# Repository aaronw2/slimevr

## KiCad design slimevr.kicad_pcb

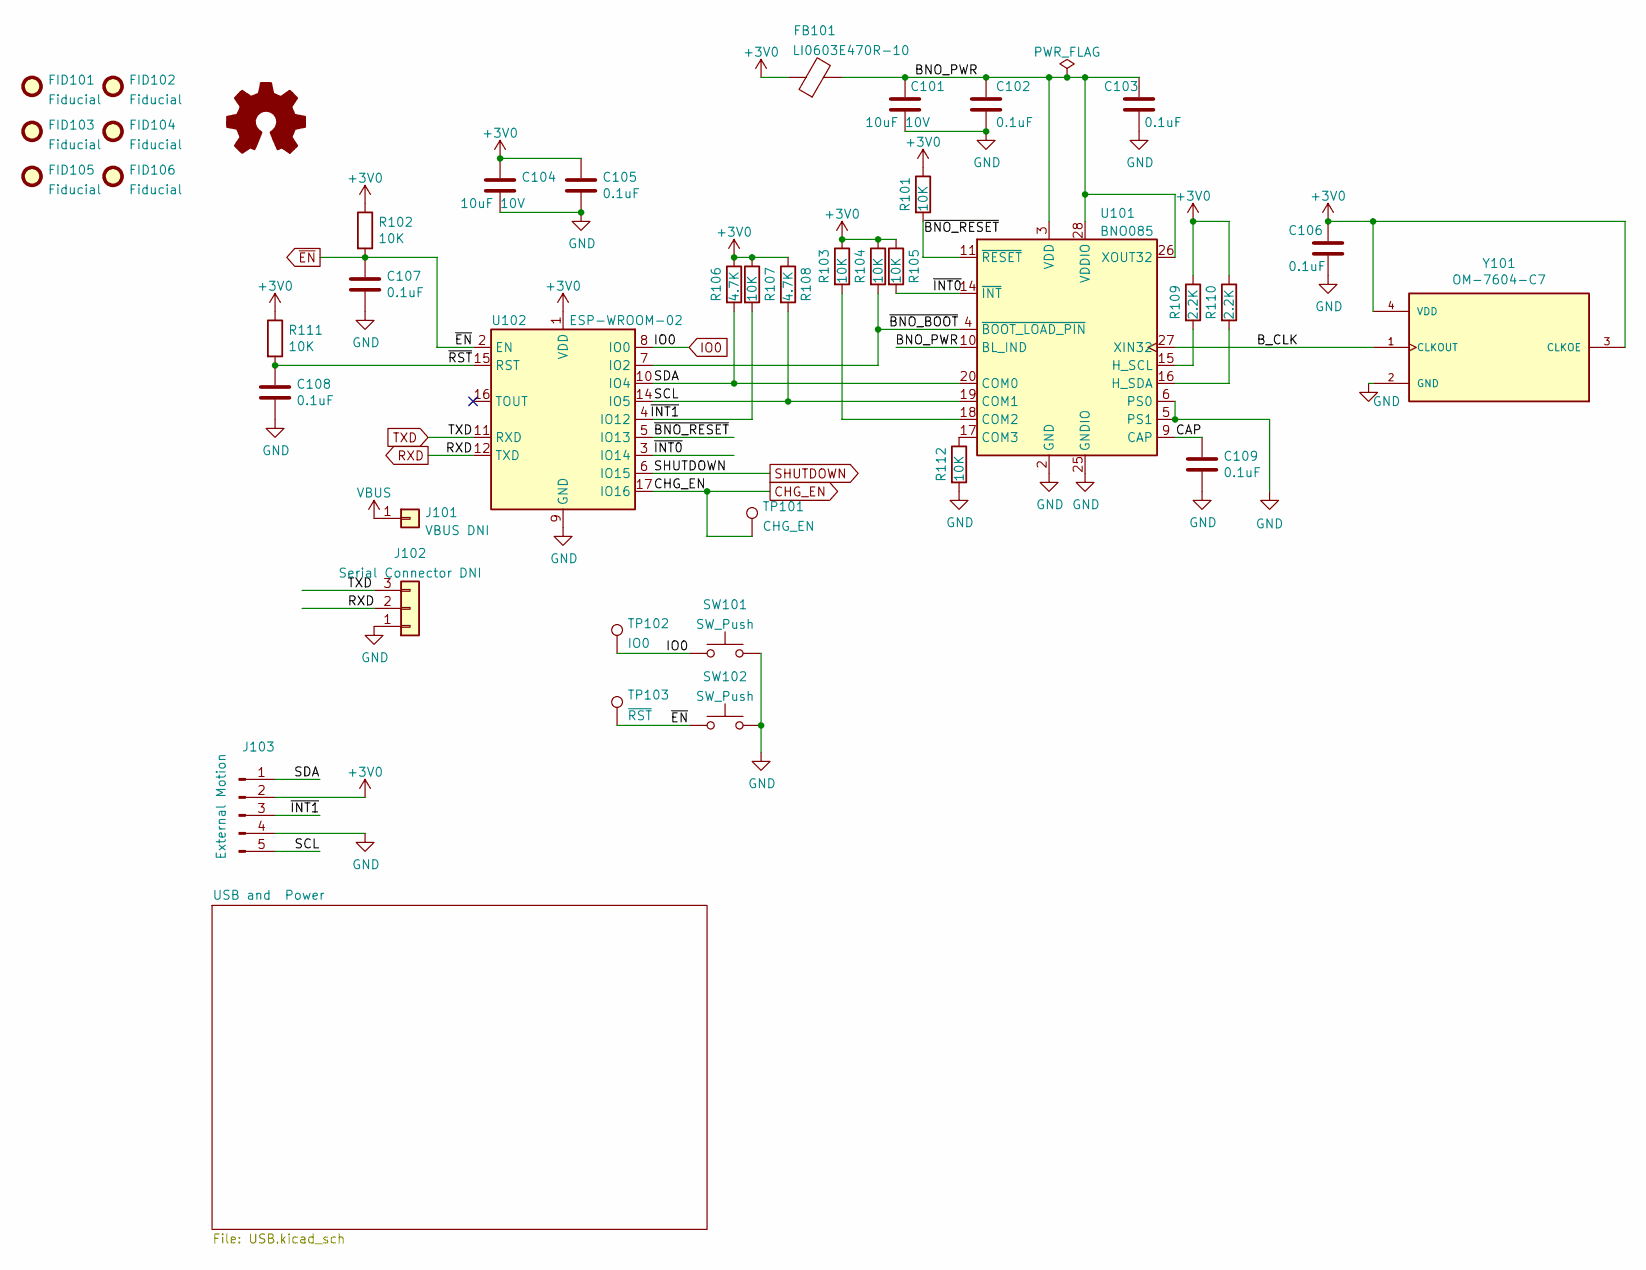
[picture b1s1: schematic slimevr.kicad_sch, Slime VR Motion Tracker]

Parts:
C101, C104: 10uF 10V; C_0603_1608Metric; MPN CL10A106MP8NNNC
C102, C103, C105, C106, C107, C108, C109: 0.1uF; C_0603_1608Metric; MPN C0603C104M3RAC7867
FB101: LI0603E470R-10; L_0603_1608Metric; MPN LI0603E470R-10
FID101, FID102, FID103, FID104, FID105, FID106: Fiducial; Fiducial_0.5mm_Mask1mm
J101: VBUS DNI; PinHeader_1x01_P2.54mm_Vertical
J102: Serial Connector DNI; PinHeader_1x03_P2.54mm_Vertical
J103: External Motion; JST_PH_S5B-PH-K_1x05_P2.00mm_Horizontal; MPN B5B-PH-SM4-TBT(LF)(SN)
LOGO101: Logo_Open_Hardware_Small; OSHW-Logo2_7.3x6mm_SilkScreen
R101, R102, R103, R104, R105, R107, R111, R112: 10K; R_0603_1608Metric; MPN RC0603FR-0710KL
R106, R108: 4.7K; R_0603_1608Metric; MPN RC0603FR-074K7L
R109, R110: 2.2K; R_0603_1608Metric; MPN RC0603FR-074K7L
SW101, SW102: SW_Push; SW_SPST_CK_KXT3; MPN KXT 331 LHS
TP101: CHG_EN; TestPoint_THTPad_1.0x1.0mm_Drill0.5mm
TP102: IO0; TestPoint_THTPad_1.0x1.0mm_Drill0.5mm
TP103: ~{RST}; TestPoint_THTPad_1.0x1.0mm_Drill0.5mm
U101: BNO085; LGA-28_5.2x3.8mm_P0.5mm; MPN BNO085
U102: ESP-WROOM-02; MPN ESP-WROOM-02D (4MB)
Y101: OM-7604-C7; OSC_OM-7604-C7; PARTREV 4.2/06.2019

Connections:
+3V0: C104.1, C105.1, C106.1, FB101.1, J103.2, R101.1, R102.1, R103.1, R104.1, R105.1, R106.1, R107.1, R108.1, R109.1, R110.1, R111.1, U102.1 (VDD), Y101.3 (CLKOE), Y101.4 (VDD); also elsewhere on the board
/BNO_PWR: C101.1, C102.1, C103.1, FB101.2, U101.3 (VDD), U101.10 (BL_IND), U101.26 (XOUT32), U101.28 (VDDIO)
/B_CLK: U101.27 (XIN32), Y101.1 (CLKOUT)
/CAP: C109.1, U101.9 (CAP)
/SCL: J103.5, R108.2, U101.19 (COM1), U102.14 (IO5)
/SDA: J103.1, R106.2, U101.20 (COM0), U102.10 (IO4)
/~BNO_BOOT: R104.2, U101.4 (~BOOT_LOAD_PIN), U102.7 (IO2)
/~BNO_RESET: R101.2, U101.11 (~RESET), U102.5 (IO13)
/~INT0: R105.2, U101.14 (~INT), U102.3 (IO14)
/~INT1: J103.3, R107.2, U102.4 (IO12)
/~RST: C108.1, R111.2, U102.15 (RST)
CHG_EN: TP101.1, U102.17 (IO16); also elsewhere on the board
GND: C101.2, C102.2, C103.2, C104.2, C105.2, C106.2, C107.2, C108.2, C109.2, J102.1, J103.4, R112.2, SW101.2, SW102.2, U101.2 (GND), U101.5 (PS1), U101.6 (PS0), U101.25 (GNDIO), U102.9 (GND), U102.13 (GND), U102.18 (GND), U102.19 (GND), Y101.2 (GND); also elsewhere on the board
IO0: SW101.1, TP102.1, U102.8 (IO0); also elsewhere on the board
unnamed: R103.2, U101.18 (COM2)
unnamed: R112.1, U101.17 (COM3)
unnamed: R109.2, U101.15 (H_SCL)
unnamed: R110.2, U101.16 (H_SDA)
RXD: J102.2, U102.12 (TXD); also elsewhere on the board
SHUTDOWN: U102.6 (IO15); also elsewhere on the board
TXD: J102.3, U102.11 (RXD); also elsewhere on the board
VBUS: J101.1; also elsewhere on the board
~EN: C107.1, R102.2, SW102.1, TP103.1, U102.2 (EN); also elsewhere on the board

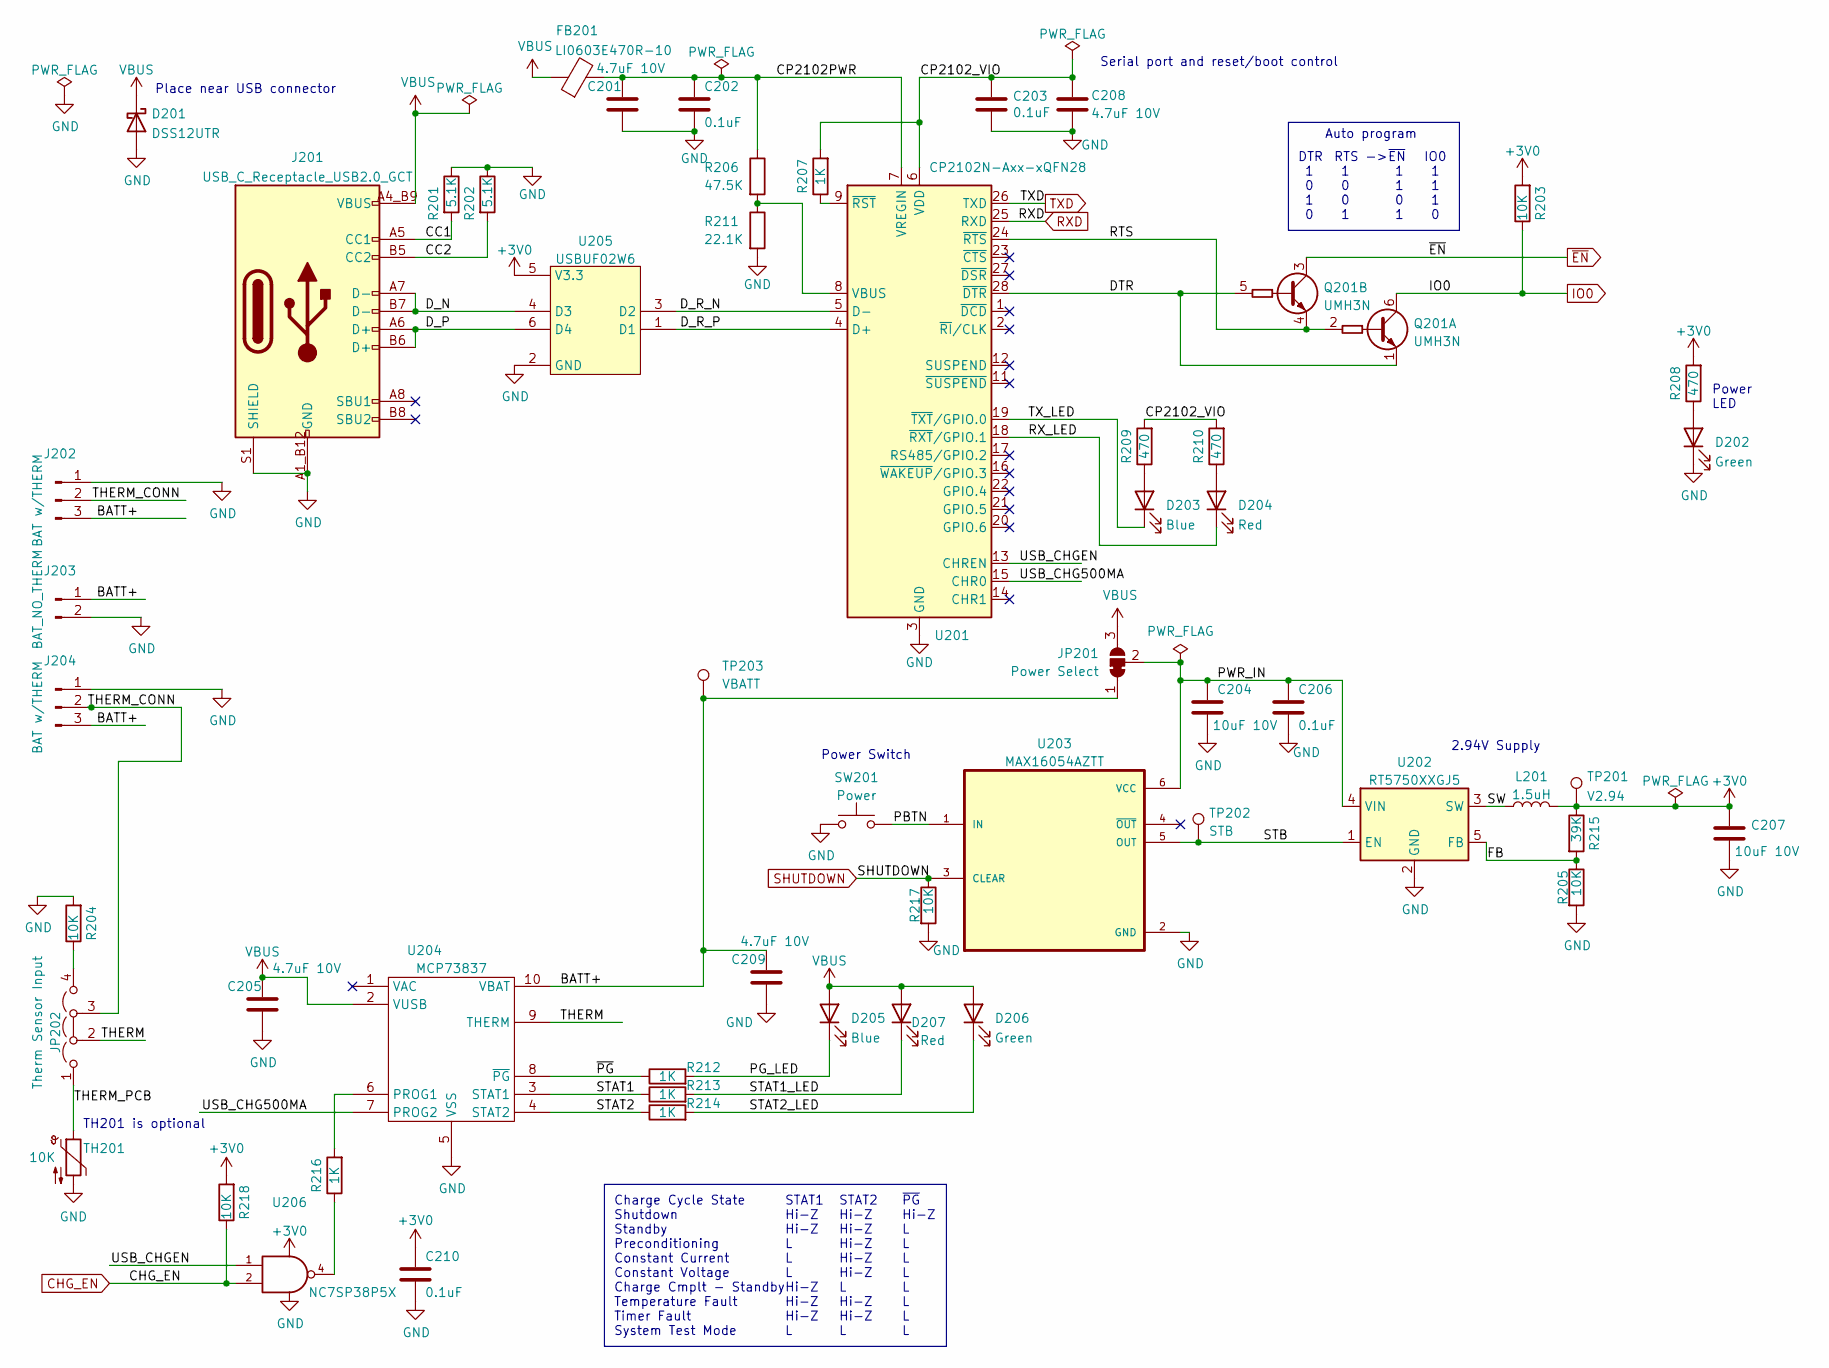
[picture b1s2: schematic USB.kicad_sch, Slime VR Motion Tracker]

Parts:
C201, C205, C208, C209: 4.7uF 10V; C_0603_1608Metric; MPN CL10A475KP8NNNC
C202, C203, C206, C210: 0.1uF; C_0603_1608Metric; MPN C0603C104M3RAC7867
C204, C207: 10uF 10V; C_0603_1608Metric; MPN CL10A106MP8NNNC
D201: DSS12UTR; D_SOD-123F; MPN DSS12UTR
D202, D206: Green; LED_0603_1608Metric; MPN 150060VS55040
D203, D205: Blue; LED_0603_1608Metric; MPN 150060BS55040
D204, D207: Red; LED_0603_1608Metric; MPN 150060SS55040
FB201: LI0603E470R-10; L_0603_1608Metric; MPN LI0603E470R-10
J201: USB_C_Receptacle_USB2.0_GCT; GCT_USB4105-GF-A; MPN USB4105-GF-A
J202: BAT w/THERM; SolderWire-0.1sqmm_1x03_P3.6mm_D0.4mm_OD1mm
J203: BAT_NO_THERM; JST_PH_S2B-PH-K_1x02_P2.00mm_Horizontal; MPN B2B-PH-SM4-TB(LF)(SN)
J204: BAT w/THERM; Molex_PicoBlade_53048-0310_1x03_P1.25mm_Horizontal; MPN 0530480350
JP201: Power Select; SolderJumper-3_P1.3mm_Bridged12_RoundedPad1.0x1.5mm
JP202: Therm Sensor Input; SolderJumper-4_P1.3mm_Bridged23_RoundedPad1.0x1.5mm
L201: 1.5uH; L_1008_2520Metric; MPN DFE252010F-1R5M=P2
Q201: UMH3N; SOT-363_SC-70-6
R201, R202: 5.1K; R_0603_1608Metric; MPN RC0603FR-075K1L
R203, R204, R205, R217, R218: 10K; R_0603_1608Metric; MPN RC0402FR-070RL
R206: 47.5K; R_0603_1608Metric
R207, R212, R213, R214, R216: 1K; R_0603_1608Metric; MPN RC0603FR-071KL
R208, R209, R210: 470; R_0603_1608Metric; MPN RC0603FR-07470RL
R211: 22.1K; R_0603_1608Metric
R215: 39K; R_0603_1608Metric; MPN RC0603FR-0739KL
SW201: Power; Panasonic_EVQPUL_EVQPUC; MPN EVQ-PUD02K
TH201: 10K; R_0603_1608Metric; MPN NCU18XH103E60RB
TP201: V2.94; TestPoint_Keystone_5000-5004_Miniature
TP202: STB; TestPoint_THTPad_1.0x1.0mm_Drill0.5mm
TP203: VBATT; TestPoint_THTPad_1.0x1.0mm_Drill0.5mm
U201: CP2102N-Axx-xQFN28; QFN-28-1EP_5x5mm_P0.5mm_EP3.35x3.35mm; MPN CP2102N-A02-GQFN28R
U202: RT5750XXGJ5; TSOT-23-5; MPN RT5750BHGJ5
U203: MAX16054AZTT; TSOT-23-6; MPN MAX16054AZT+T
U204: MCP73837; DFN-10-1EP_3x3mm_P0.5mm_EP1.55x2.48mm; MPN MCP73837-FJI/MF
U205: USBUF02W6; SOT-323-6L
U206: NC7SP38P5X; SOT-353_SC-70-5

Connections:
+3V0: C207.1, C210.1, L201.2, R203.2, R208.2, R215.1, R218.2, TP201.1, U205.5 (V3.3), U206.5 (VCC); also elsewhere on the board
/USB and Power/BATT+: C209.1, J202.3, J203.1, J204.3, JP201.1 (A), TP203.1, U204.10 (VBAT)
/USB and Power/CC1: J201.A5 (CC1), R201.2
/USB and Power/CC2: J201.B5 (CC2), R202.2
/USB and Power/CP2102PWR: C201.1, C202.1, FB201.2, R206.1, U201.7 (VREGIN)
/USB and Power/CP2102_VIO: C203.1, C208.1, R207.2, R209.2, R210.2, U201.6 (VDD)
/USB and Power/DTR: Q201.1 (E1), Q201.5 (B2), U201.28 (~DTR)
/USB and Power/D_N: J201.A7 (D-), J201.B7 (D-), U205.4 (D3)
/USB and Power/D_P: J201.A6 (D+), J201.B6 (D+), U205.6 (D4)
/USB and Power/D_R_N: U201.5 (D-), U205.3 (D2)
/USB and Power/D_R_P: U201.4 (D+), U205.1 (D1)
/USB and Power/FB: R205.1, R215.2, U202.5 (FB)
/USB and Power/PBTN: SW201.2, U203.1 (IN)
/USB and Power/PG_LED: D205.1 (K), R212.2
/USB and Power/PWR_IN: C204.1, C206.1, JP201.2 (C), U202.4 (VIN), U203.6 (VCC)
/USB and Power/RTS: Q201.2 (B1), Q201.4 (E2), U201.24 (~RTS)
/USB and Power/RX_LED: D204.1 (K), U201.18 (~RXT/GPIO.1)
/USB and Power/STAT1: R213.1, U204.3 (STAT1)
/USB and Power/STAT1_LED: D207.1 (K), R213.2
/USB and Power/STAT2: R214.1, U204.4 (STAT2)
/USB and Power/STAT2_LED: D206.1 (K), R214.2
/USB and Power/STB: TP202.1, U202.1 (EN), U203.5 (OUT)
/USB and Power/SW: L201.1, U202.3 (SW)
/USB and Power/THERM: JP202.2 (C), U204.9 (THERM)
/USB and Power/THERM_CONN: J202.2, J204.2, JP202.3 (B)
/USB and Power/THERM_PCB: JP202.1 (A), TH201.1
/USB and Power/TX_LED: D203.1 (K), U201.19 (~TXT/GPIO.0)
/USB and Power/USB_CHG500MA: U201.15 (CHR0), U204.7 (PROG2)
/USB and Power/USB_CHGEN: U201.13 (CHREN), U206.1 (A)
/USB and Power/~PG: R212.1, U204.8 (~PG)
CHG_EN: R218.1, U206.2 (B); also elsewhere on the board
GND: C201.2, C202.2, C203.2, C204.2, C205.2, C206.2, C207.2, C208.2, C209.2, C210.2, D201.2 (A), D202.1 (K), J201.A1_B12 (GND), J201.B1_A12 (GND), J201.S1 (SHIELD), J201.S2 (SHIELD), J201.S3 (SHIELD), J201.S4 (SHIELD), J202.1, J203.2, J204.1, R201.1, R202.1, R204.2, R205.2, R211.2, R217.2, SW201.1, TH201.2, U201.3 (GND), U201.29 (GND), U202.2 (GND), U203.2 (GND), U204.5 (VSS), U204.11 (VSS), U205.2 (GND), U206.3 (GND); also elsewhere on the board
IO0: Q201.6 (C1), R203.1; also elsewhere on the board
unnamed: D202.2 (A), R208.1
unnamed: D203.2 (A), R209.1
unnamed: D204.2 (A), R210.1
unnamed: JP202.4, R204.1
unnamed: R206.2, R211.1, U201.8 (VBUS)
unnamed: R207.1, U201.9 (~RST)
unnamed: R216.1, U206.4 (Y)
unnamed: R216.2, U204.6 (PROG1)
RXD: U201.25 (RXD); also elsewhere on the board
SHUTDOWN: R217.1, U203.3 (CLEAR); also elsewhere on the board
TXD: U201.26 (TXD); also elsewhere on the board
VBUS: C205.1, D201.1 (K), D205.2 (A), D206.2 (A), D207.2 (A), FB201.1, J201.A4_B9 (VBUS), J201.B4_A9 (VBUS), JP201.3 (B), U204.2 (VUSB); also elsewhere on the board
~EN: Q201.3 (C2); also elsewhere on the board

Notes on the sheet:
Power Switch
Charge Cycle State Shutdown Standby Preconditioning Constant Current Constant Voltage Charge Cmplt - Standby Temperature Fault Timer Fault System Test Mode
Auto program
STAT1 Hi-Z Hi-Z L L L Hi-Z Hi-Z Hi-Z L
Place near USB connector
TH201 is optional
Power LED
RTS -> 1 0 0 1
IO0 1 1 1 0
~{EN} 1 1 0 1
STAT2 Hi-Z Hi-Z Hi-Z Hi-Z Hi-Z L Hi-Z Hi-Z L
DTR 1 0 1 0
2.94V Supply
~{PG} Hi-Z L L L L L L L L
Serial port and reset/boot control

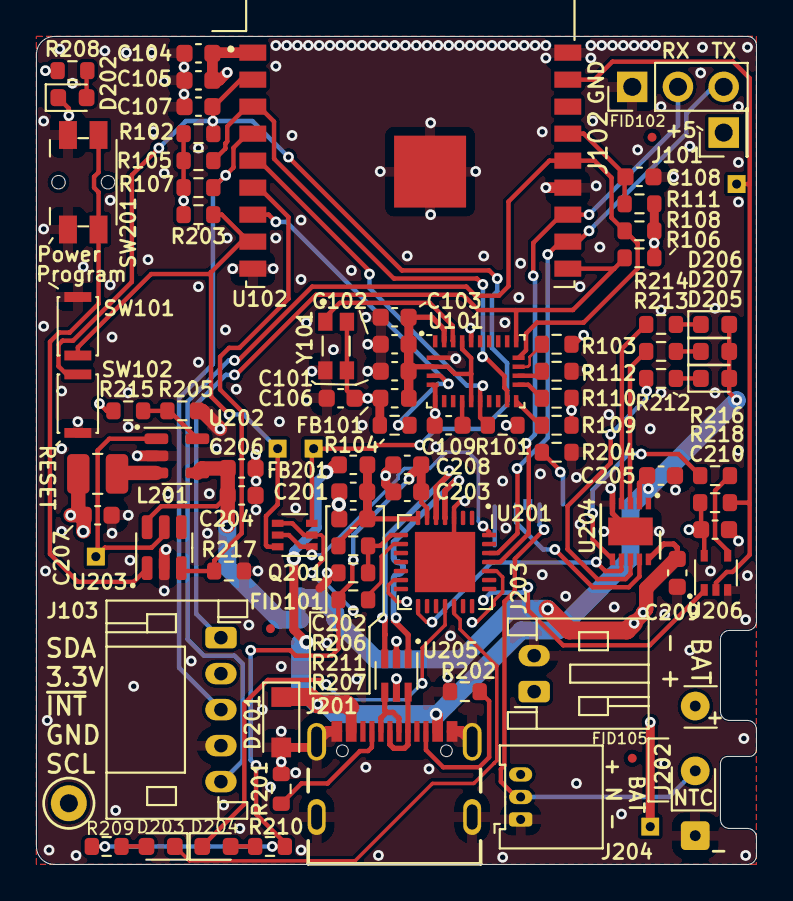
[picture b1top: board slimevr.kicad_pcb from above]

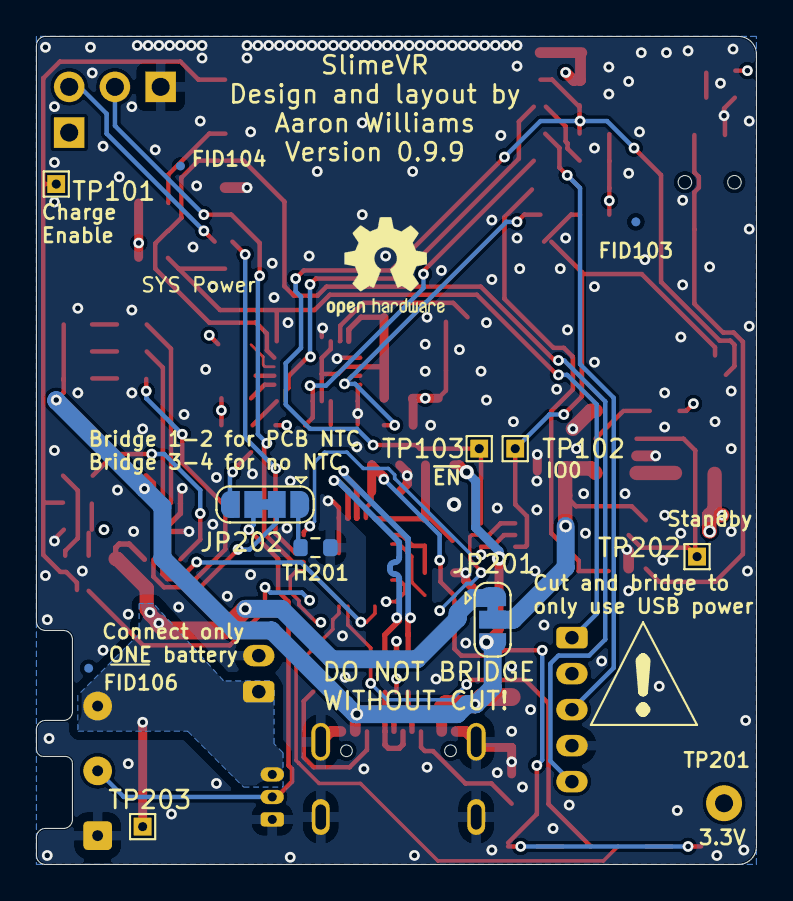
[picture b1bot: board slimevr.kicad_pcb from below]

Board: 4 copper layers, 40.0 x 46.0 mm, 95 parts (12 on the bottom side), 60 nets.

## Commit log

2022-04-06 Initial checkin of version 0.9.9 with license
2022-04-06 Minor cleanup

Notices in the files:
slimevr.kicad_pcb:
Copyright © 2022 Aaron Williams
